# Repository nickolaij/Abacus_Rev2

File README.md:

# Abacus Mechanical Keyboard

A 45% mechanical keyboard that includes an encoder volume/scroll wheel and RGB lighting. 

This keyboard is powered by QMK, visit the [QMK Repository](https://github.com/qmk/qmk_firmware/) to see all the amazing keyboards supported by them.

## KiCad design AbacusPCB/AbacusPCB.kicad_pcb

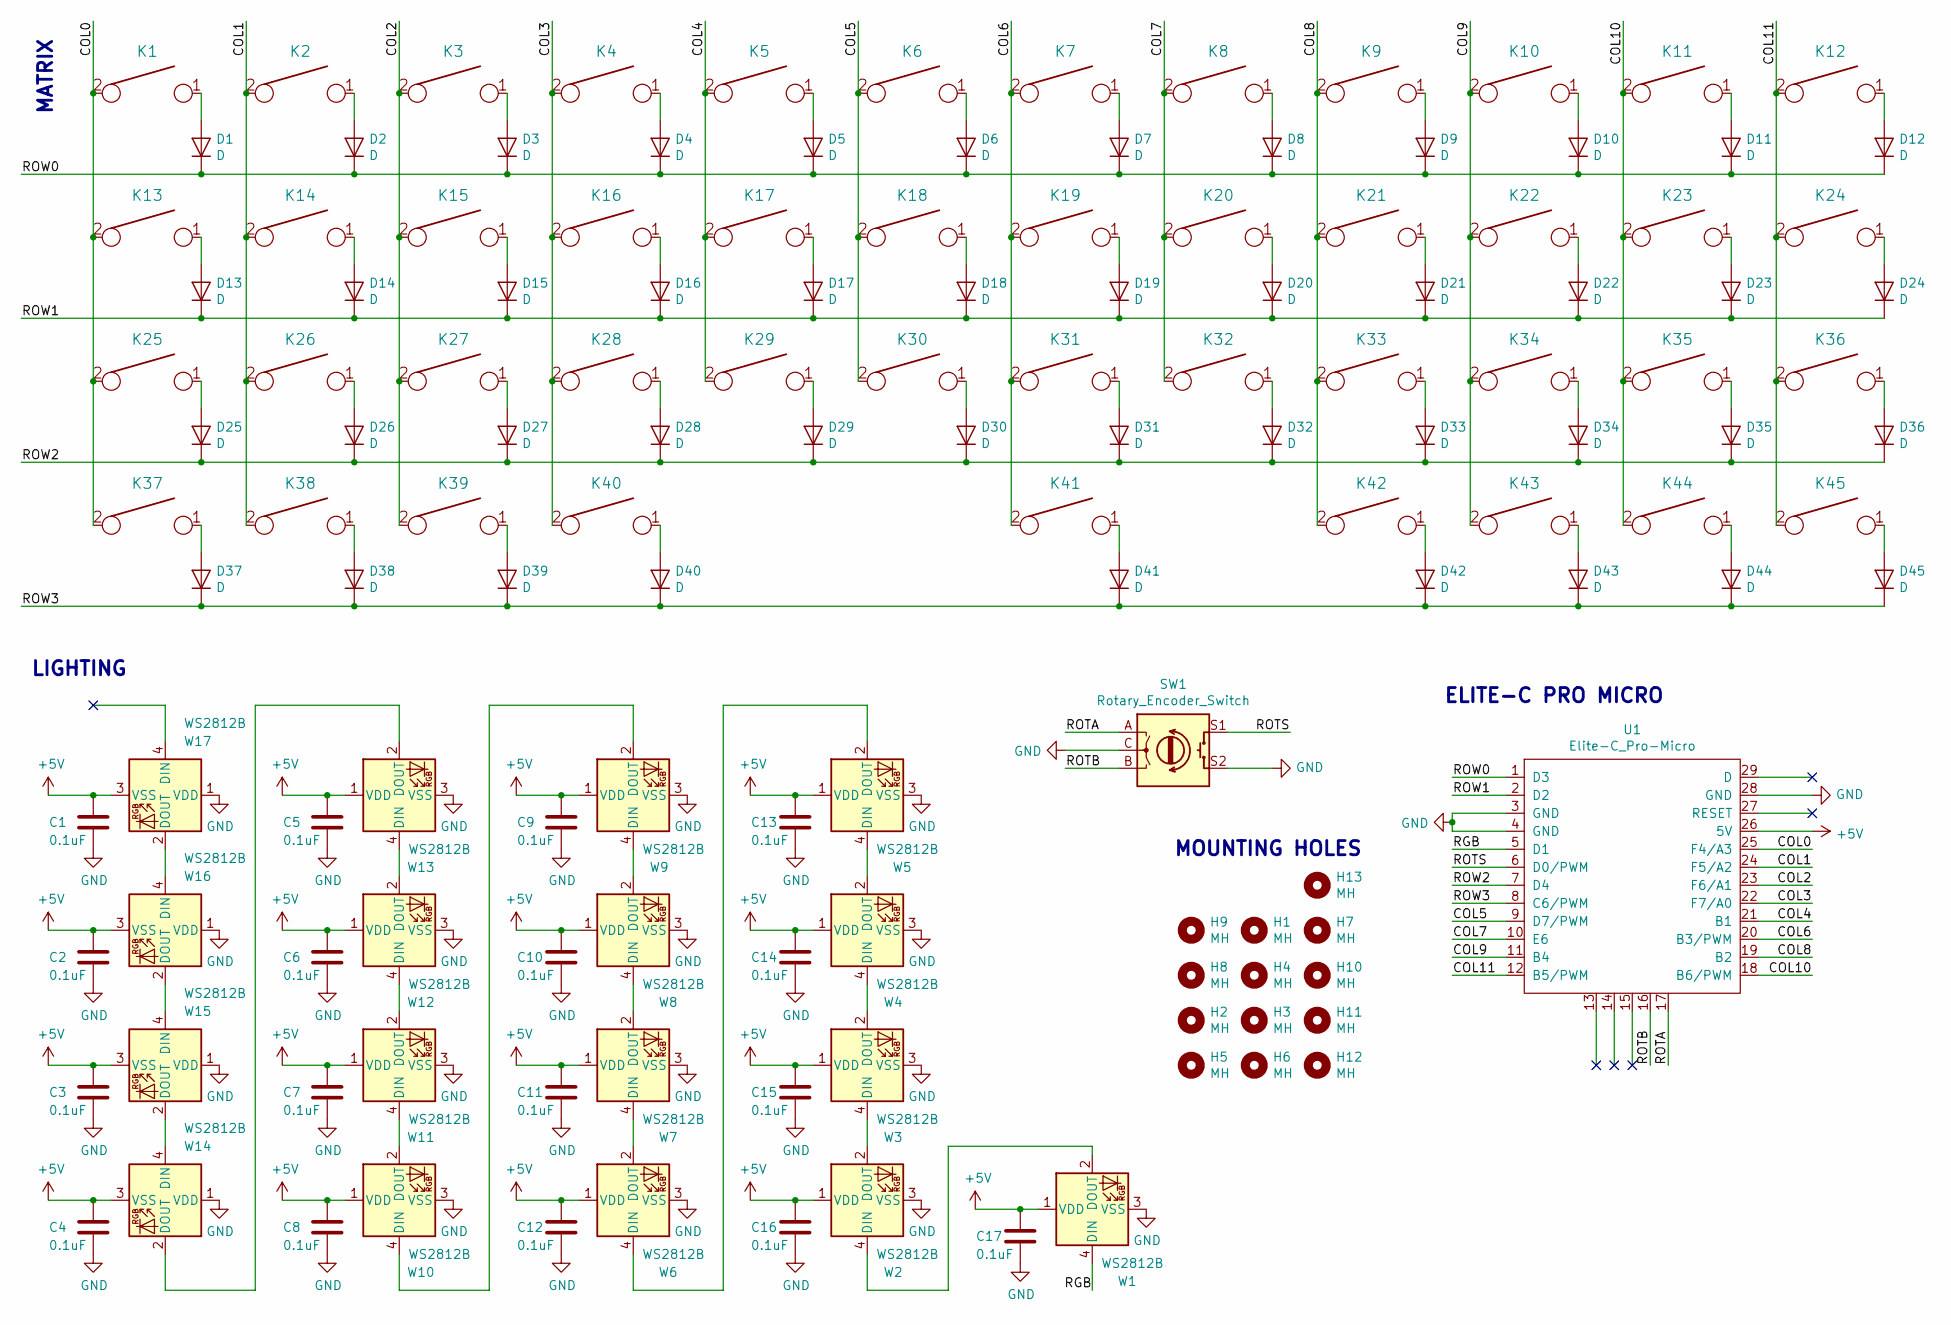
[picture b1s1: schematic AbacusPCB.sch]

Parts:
C1, C2, C3, C4, C5, C6, C7, C8, C9, C10, C11, C12, C13, C14, C15, C16, C17: 0.1uF; C_0603_1608Metric_Pad1.05x0.95mm_HandSolder
D1, D2, D3, D4, D5, D6, D7, D8, D9, D10, D11, D12, D13, D14, D15, D16, D17, D18, D19, D20, D21, D22, D23, D24, D25, D26, D27, D28, D29, D30, D31, D32, D33, D34, D35, D36, D37, D38, D39, D40, D41, D42, D43, D44, D45: D; Diode
H1, H2, H3, H4, H5, H6, H7, H8, H9, H10, H11, H12, H13: MH; M3 Hole
K1, K2, K3, K4, K5, K6, K7, K8, K9, K10, K11, K14, K15, K16, K17, K18, K19, K20, K21, K22, K23, K26, K27, K28, K29, K30, K31, K32, K33, K34, K35, K36, K38, K39, K42, K43, K44, K45: KEYSW; MX-1U-NoLED
K12, K25: KEYSW; MX-1.75U-NoLED
K13, K37: KEYSW; MX-1.25U-NoLED
K24: KEYSW; MX-1.5U-NoLED
K40, K41: KEYSW; MX-2.75U-ReversedStabilizers-NoLED
SW1: Rotary_Encoder_Switch; Encoder
U1: Elite-C_Pro-Micro; Elite-C Pro-Micro
W1, W2, W3, W4, W5, W6, W7, W8, W9, W10, W11, W12, W13, W14, W15, W16, W17: WS2812B; WS2812_Hand_Solder

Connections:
+5V: C1.1, C2.1, C3.1, C4.1, C5.1, C6.1, C7.1, C8.1, C9.1, C10.1, C11.1, C12.1, C13.1, C14.1, C15.1, C16.1, C17.1, U1.26 (5V), W1.1 (VDD), W2.1 (VDD), W3.1 (VDD), W4.1 (VDD), W5.1 (VDD), W6.1 (VDD), W7.1 (VDD), W8.1 (VDD), W9.1 (VDD), W10.1 (VDD), W11.1 (VDD), W12.1 (VDD), W13.1 (VDD), W14.3 (VSS), W15.3 (VSS), W16.3 (VSS), W17.3 (VSS)
/COL0: K1.2, K13.2, K25.2, K37.2, U1.25 (F4/A3)
/COL1: K2.2, K14.2, K26.2, K38.2, U1.24 (F5/A2)
/COL2: K3.2, K15.2, K27.2, K39.2, U1.23 (F6/A1)
/COL3: K4.2, K16.2, K28.2, K40.2, U1.22 (F7/A0)
/COL4: K5.2, K17.2, K29.2, U1.21 (B1)
/COL5: K6.2, K18.2, K30.2, U1.9 (D7/PWM)
/COL6: K7.2, K19.2, K31.2, K41.2, U1.20 (B3/PWM)
/COL7: K8.2, K20.2, K32.2, U1.10 (E6)
/COL8: K9.2, K21.2, K33.2, K42.2, U1.19 (B2)
/COL9: K10.2, K22.2, K34.2, K43.2, U1.11 (B4)
/COL10: K11.2, K23.2, K35.2, K44.2, U1.18 (B6/PWM)
/COL11: K12.2, K24.2, K36.2, K45.2, U1.12 (B5/PWM)
/RGB: U1.5 (D1), W1.4 (DIN)
/ROTA: SW1.A, U1.17
/ROTB: SW1.B, U1.16
/ROTS: SW1.S1, U1.6 (D0/PWM)
/ROW0: D1.1 (K), D2.1 (K), D3.1 (K), D4.1 (K), D5.1 (K), D6.1 (K), D7.1 (K), D8.1 (K), D9.1 (K), D10.1 (K), D11.1 (K), D12.1 (K), U1.1 (D3)
/ROW1: D13.1 (K), D14.1 (K), D15.1 (K), D16.1 (K), D17.1 (K), D18.1 (K), D19.1 (K), D20.1 (K), D21.1 (K), D22.1 (K), D23.1 (K), D24.1 (K), U1.2 (D2)
/ROW2: D25.1 (K), D26.1 (K), D27.1 (K), D28.1 (K), D29.1 (K), D30.1 (K), D31.1 (K), D32.1 (K), D33.1 (K), D34.1 (K), D35.1 (K), D36.1 (K), U1.7 (D4)
/ROW3: D37.1 (K), D38.1 (K), D39.1 (K), D40.1 (K), D41.1 (K), D42.1 (K), D43.1 (K), D44.1 (K), D45.1 (K), U1.8 (C6/PWM)
GND: C1.2, C2.2, C3.2, C4.2, C5.2, C6.2, C7.2, C8.2, C9.2, C10.2, C11.2, C12.2, C13.2, C14.2, C15.2, C16.2, C17.2, SW1.C, SW1.S2, U1.3 (GND), U1.4 (GND), U1.28 (GND), W1.3 (VSS), W2.3 (VSS), W3.3 (VSS), W4.3 (VSS), W5.3 (VSS), W6.3 (VSS), W7.3 (VSS), W8.3 (VSS), W9.3 (VSS), W10.3 (VSS), W11.3 (VSS), W12.3 (VSS), W13.3 (VSS), W14.1 (VDD), W15.1 (VDD), W16.1 (VDD), W17.1 (VDD)
unnamed: D1.2 (A), K1.1
unnamed: D2.2 (A), K2.1
unnamed: D3.2 (A), K3.1
unnamed: D4.2 (A), K4.1
unnamed: D5.2 (A), K5.1
unnamed: D6.2 (A), K6.1
unnamed: D7.2 (A), K7.1
unnamed: D8.2 (A), K8.1
unnamed: D9.2 (A), K9.1
unnamed: D10.2 (A), K10.1
unnamed: D11.2 (A), K11.1
unnamed: D12.2 (A), K12.1
unnamed: D13.2 (A), K13.1
unnamed: D14.2 (A), K14.1
unnamed: D15.2 (A), K15.1
unnamed: D16.2 (A), K16.1
unnamed: D17.2 (A), K17.1
unnamed: D18.2 (A), K18.1
unnamed: D19.2 (A), K19.1
unnamed: D20.2 (A), K20.1
unnamed: D21.2 (A), K21.1
unnamed: D22.2 (A), K22.1
unnamed: D23.2 (A), K23.1
unnamed: D24.2 (A), K24.1
unnamed: D25.2 (A), K25.1
unnamed: D26.2 (A), K26.1
unnamed: D27.2 (A), K27.1
unnamed: D28.2 (A), K28.1
unnamed: D29.2 (A), K29.1
unnamed: D30.2 (A), K30.1
unnamed: D31.2 (A), K31.1
unnamed: D32.2 (A), K32.1
unnamed: D33.2 (A), K33.1
unnamed: D34.2 (A), K34.1
unnamed: D35.2 (A), K35.1
unnamed: D36.2 (A), K36.1
unnamed: D37.2 (A), K37.1
unnamed: D38.2 (A), K38.1
unnamed: D39.2 (A), K39.1
unnamed: D40.2 (A), K40.1
unnamed: D41.2 (A), K41.1
unnamed: D42.2 (A), K42.1
unnamed: D43.2 (A), K43.1
unnamed: D44.2 (A), K44.1
unnamed: D45.2 (A), K45.1
unnamed: W1.2 (DOUT), W2.4 (DIN)
unnamed: W2.2 (DOUT), W3.4 (DIN)
unnamed: W3.2 (DOUT), W4.4 (DIN)
unnamed: W4.2 (DOUT), W5.4 (DIN)
unnamed: W5.2 (DOUT), W6.4 (DIN)
unnamed: W6.2 (DOUT), W7.4 (DIN)
unnamed: W7.2 (DOUT), W8.4 (DIN)
unnamed: W8.2 (DOUT), W9.4 (DIN)
unnamed: W10.2 (DOUT), W11.4 (DIN)
unnamed: W9.2 (DOUT), W10.4 (DIN)
unnamed: W11.2 (DOUT), W12.4 (DIN)
unnamed: W12.2 (DOUT), W13.4 (DIN)
unnamed: W13.2 (DOUT), W14.2 (DOUT)
unnamed: W14.4 (DIN), W15.2 (DOUT)
unnamed: W15.4 (DIN), W16.2 (DOUT)
unnamed: W16.4 (DIN), W17.2 (DOUT)

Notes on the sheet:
MATRIX
MOUNTING HOLES
LIGHTING
ELITE-C PRO MICRO

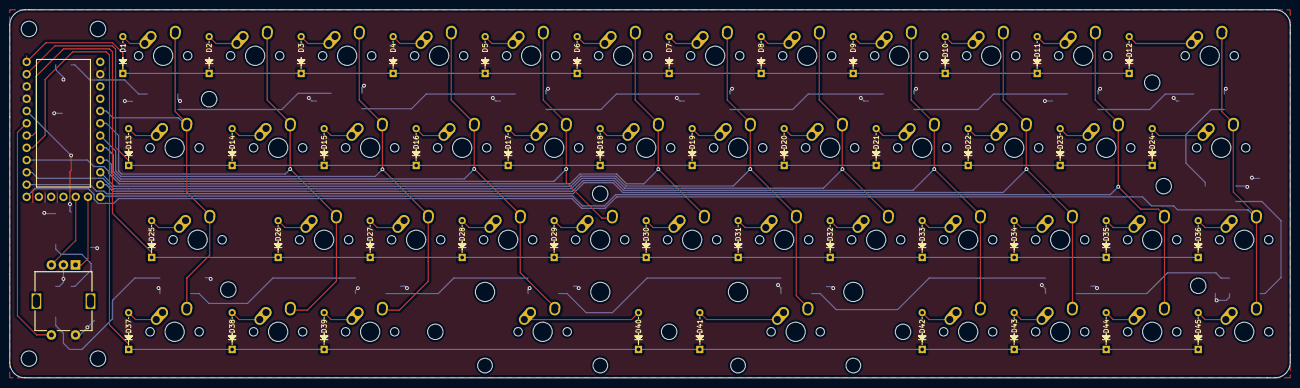
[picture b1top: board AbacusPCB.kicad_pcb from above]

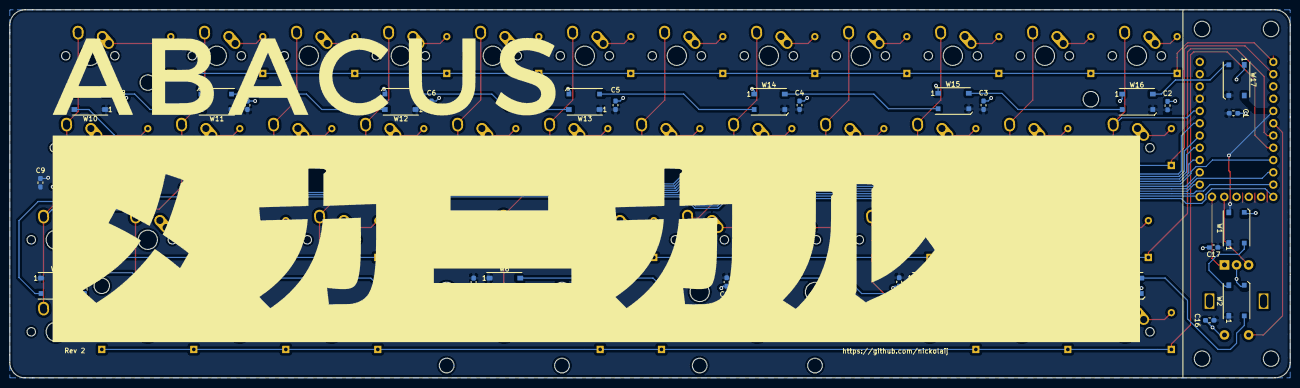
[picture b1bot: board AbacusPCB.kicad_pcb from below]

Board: 2 copper layers, 265.1 x 76.2 mm, 139 parts (35 on the bottom side), 83 nets.

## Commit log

2020-02-06 first
2020-02-09 gerbers sent
2020-02-09 celebatory push
2020-03-04 finalisation changes for public release
2020-03-04 Create LICENSE
